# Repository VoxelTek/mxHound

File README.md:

# mxHound
### A Wii RTC-RVL ("MX chip") relocation flex

This flexible PCB aims to simplify the relocation of the Wii MX chip, to make creating portables that utilise it as easy as possible.

Due to the overlapping of the via used for the U10, I decided to also relocate it onto here. I also added a solder pad if U10 emulation (like what's featured on the RVL-PMS line) is used, or if U10 is located elsewhere. 

Additional pads were added for soft shutdown and the EXI bus, primarily for the RVL-DD.

This flex primarily reuses the original components found on the Wii motherboard, with the reference designators for the passive components matching the corresponding components from the Wii.

- R60 = 1kΩ, 0402 (1005 metric)
- D31 = 0603 (1608 metric) package, unknown specs
- C101, C102 = 5pF, 0402 (1005 metric)
- C98 = 100nF, 0402 (1005 metric)

To reduce space, the crystal has been swapped for a smaller one. Any crystal with a frequency of 32.768 kHz and a load capacitance of 4pF in a 2mm x 1.2mm package should work fine.

Some suitable replacements:

- ABS06-107-32.768KHZ-T ([Digikey](https://www.digikey.com.au/en/products/detail/abracon-llc/ABS06-107-32-768KHZ-T/4291565) | [Mouser](https://mou.sr/3IUZvTK))
- ECS-.327-CDX-1082 ([Digikey](https://www.digikey.com.au/en/products/detail/ecs-inc/ECS-327-CDX-1082/5875549) | [Mouser](https://mou.sr/3VA6LMf))

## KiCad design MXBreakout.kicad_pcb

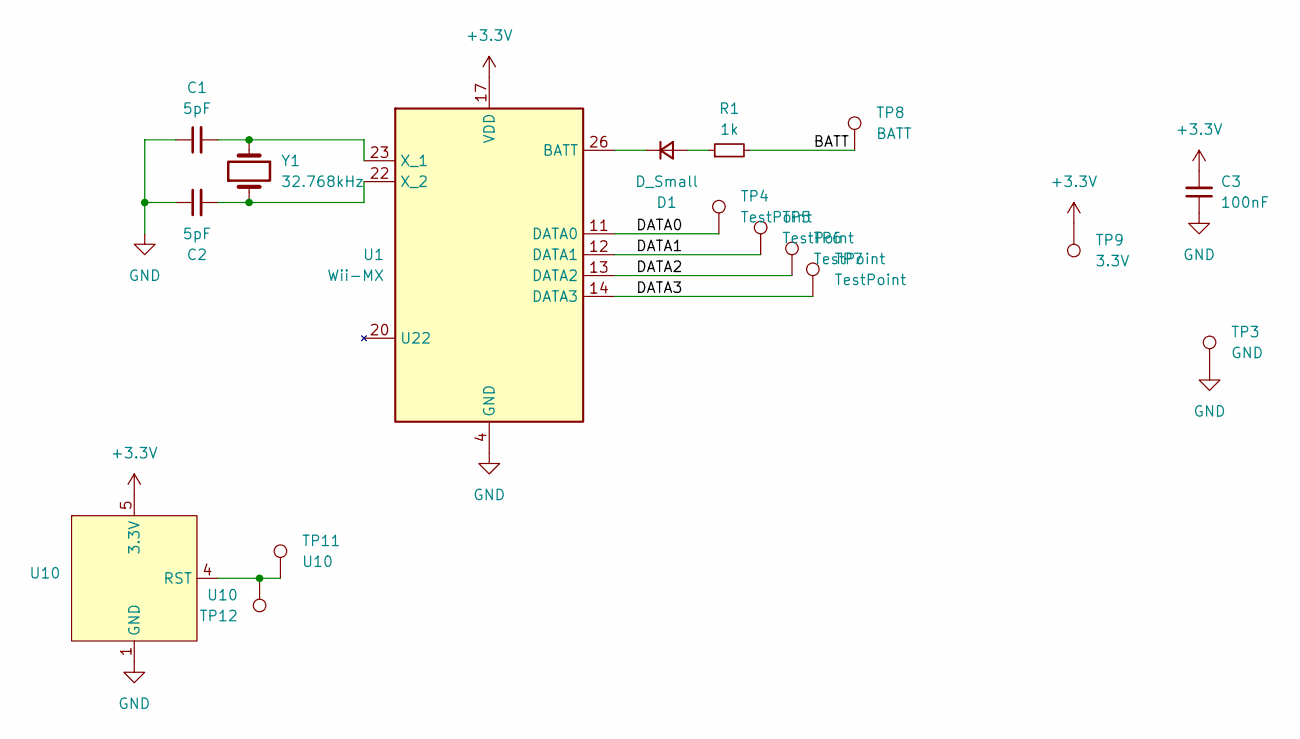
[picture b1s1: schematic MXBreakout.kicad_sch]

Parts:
C1, C2: 5pF; C_0402_1005Metric; MouserPart 81-GRM1555C1H5R0BA1D
C3: 100nF; C_0402_1005Metric
D1: D_Small; D_0603_1608Metric
R1: 1k; R_0402_1005Metric
TP3: GND; TestPoint_THTPad_D0.5mm_Drill0.35mm
TP4, TP5, TP6, TP7: TestPoint; TestPoint_THTPad_D0.5mm_Drill0.35mm
TP8: BATT; TestPoint_Pad_D1.0mm
TP9: 3.3V; TestPoint_Pad_D1.0mm
TP11: U10; TestPoint_THTPad_D0.5mm_Drill0.35mm
TP12: U10; TestPoint_Pad_D1.0mm
U1: Wii-MX; SOIC-28W_7.5x17.9mm_P1.27mm
U10: SOT-23-5
Y1: 32.768kHz; Crystal_SMD_2012-2Pin_2.0x1.2mm

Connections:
+3.3V: C3.2, TP9.1, U1.17 (VDD), U1.24 (VDD), U1.25 (VDD), U1.27 (VDD), U10.5 (3.3V)
/BATT: R1.2, TP8.1
/DATA0: TP4.1, U1.11 (DATA0)
/DATA1: TP5.1, U1.12 (DATA1)
/DATA2: TP6.1, U1.13 (DATA2)
/DATA3: TP7.1, U1.14 (DATA3)
GND: C1.1, C2.1, C3.1, TP3.1, U1.4 (GND), U1.16 (GND), U10.1 (GND), U10.2 (GND), U10.3 (GND); also elsewhere on the board
unnamed: D1.2 (A), R1.1
unnamed: D1.1 (K), U1.26 (BATT)
unnamed: C1.2, U1.23 (X_1), Y1.2
unnamed: C2.2, U1.22 (X_2), Y1.1
unnamed: TP11.1, TP12.1, U10.4 (RST)

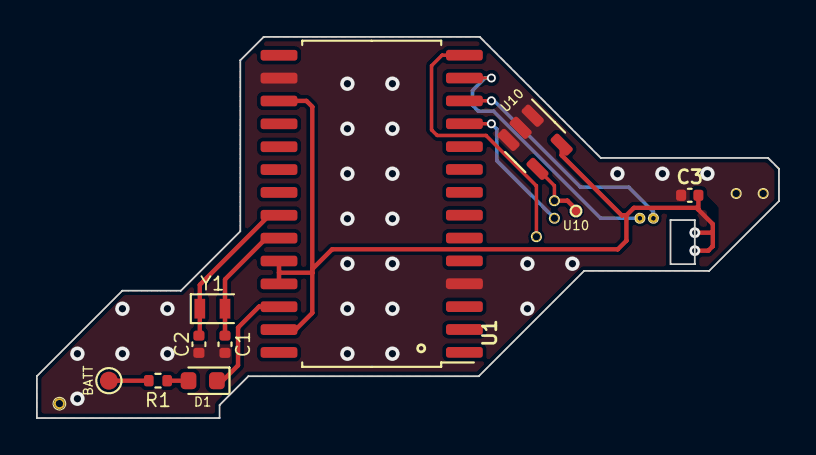
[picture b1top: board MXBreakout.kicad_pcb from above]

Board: 2 copper layers, 41.2 x 21.2 mm, 17 parts (0 on the bottom side), 12 nets.

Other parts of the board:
TP3#2: GND; TestPoint_THTPad_D0.5mm_Drill0.35mm

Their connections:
GND: TP3#2.1; also elsewhere on the board

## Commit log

2024-01-15 initial changes
2024-01-15 Basically no change
2024-01-15 nearing completion
2024-03-17 HopefullyFinal
2024-03-27 Adjust PCB 3D view
2024-03-27 Reorganisation and gerber regeneration
2024-03-27 Minor track tidy
2024-03-30 Minor cleanup
2024-03-30 Make layers visible again
2024-04-01 Fix pad alignment, add soft shutdown
2024-04-01 Regenerate gerber files
2024-04-01 Backups update
2024-04-02 Add cutouts, regenerate gerbers
2024-04-02 Remove lock, update backups
2024-04-04 More backups
2024-05-10 Add pads for EXI bus, primarily for RVL-DD
2024-05-13 Version for Wii Mini, relocates connections
2024-05-13 Clean up PCB, regenerate gerbers
2024-08-07 Backported to stable
2025-05-06 Remove "untested" warning
2025-05-06 Misc improvements to flex
2025-05-10 Regenerate gerbers
2025-05-22 Regenerated gerbers due to weird issue
